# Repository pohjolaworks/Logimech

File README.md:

# Logimech
Replacement PCB for Logitech 3D Extreme joystick. Allows use of mechanical switches and MX keycaps for the side buttons of the joystick

## How to get
Gerber folder has plotted gerbers for the Rev 1 of Logimech. 
They were used to order from PCBWay, and should work atleast there.

## Notes:

Rev 1: User has reported some buttons physical location changed, this can be  fixed by remapping.

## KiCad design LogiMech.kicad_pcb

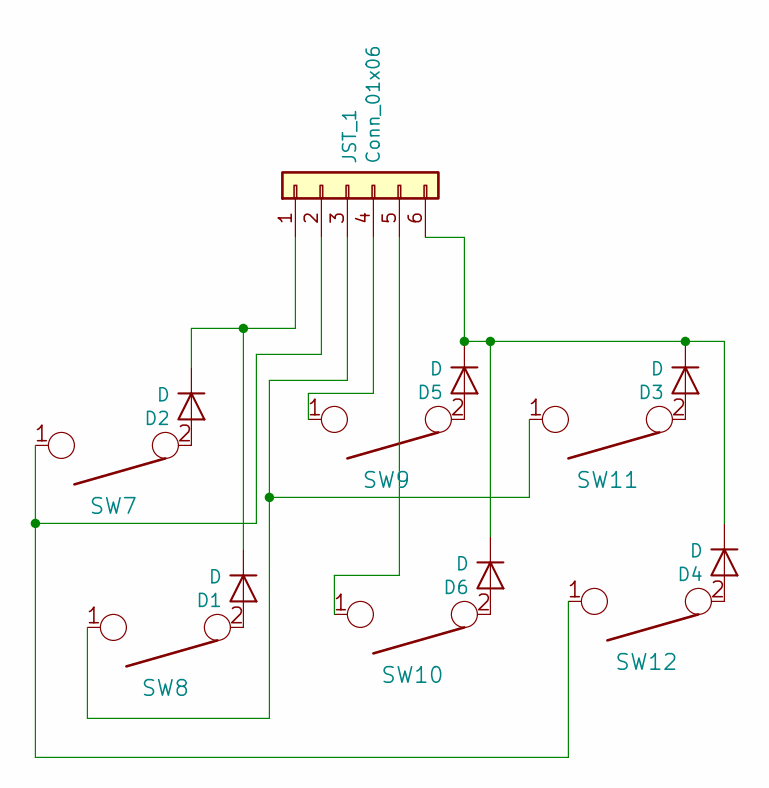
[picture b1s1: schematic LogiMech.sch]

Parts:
D1, D2, D3, D4, D5, D6: D; Diode-Hybrid-Back
JST_1: Conn_01x06; JST_XH_B6B-XH-A_1x06_P2.50mm_Vertical
SW7, SW8, SW9, SW10, SW11, SW12: KEYSW; kailh-cpg1353-reversible

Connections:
unnamed: D1.1 (K), D2.1 (K), JST_1.1
unnamed: D1.2 (A), SW8.2
unnamed: D2.2 (A), SW7.2
unnamed: D3.1 (K), D4.1 (K), D5.1 (K), D6.1 (K), JST_1.6
unnamed: D3.2 (A), SW11.2
unnamed: D4.2 (A), SW12.2
unnamed: D5.2 (A), SW9.2
unnamed: D6.2 (A), SW10.2
unnamed: JST_1.2, SW7.1, SW12.1
unnamed: JST_1.3, SW8.1, SW11.1
unnamed: JST_1.4, SW9.1
unnamed: JST_1.5, SW10.1

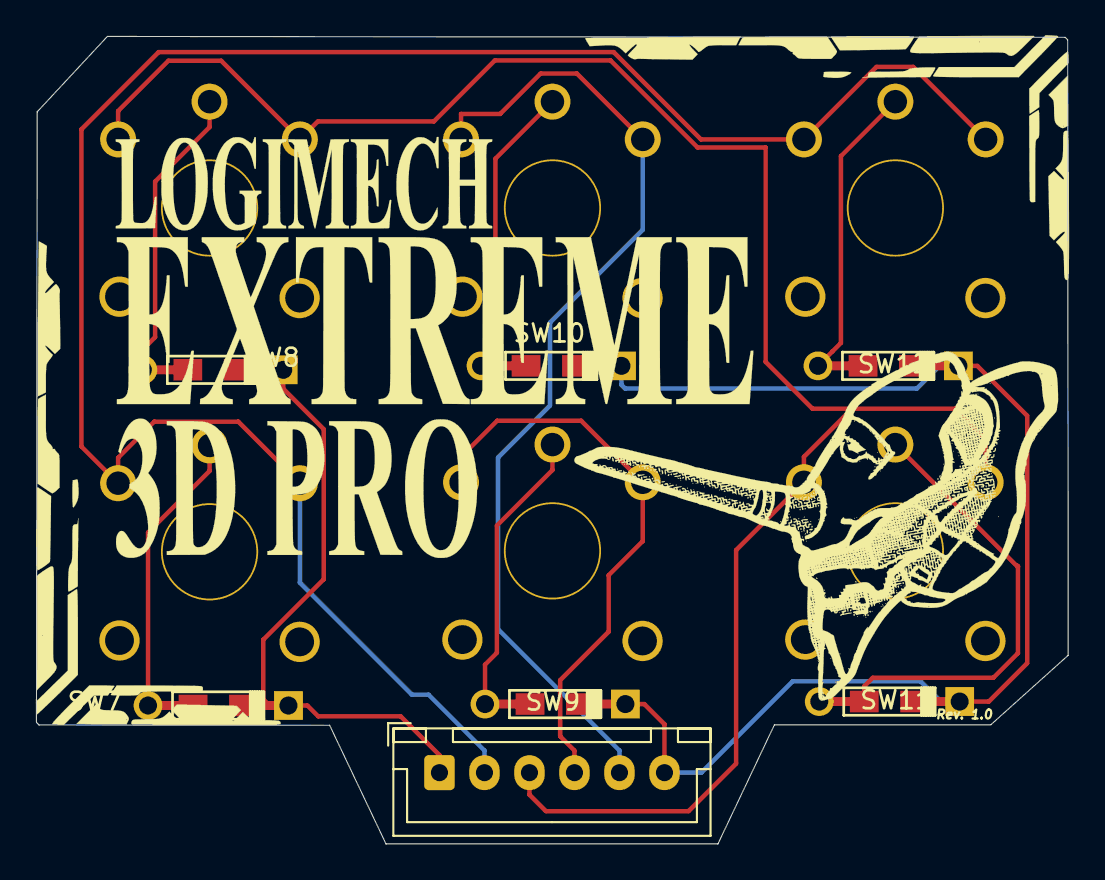
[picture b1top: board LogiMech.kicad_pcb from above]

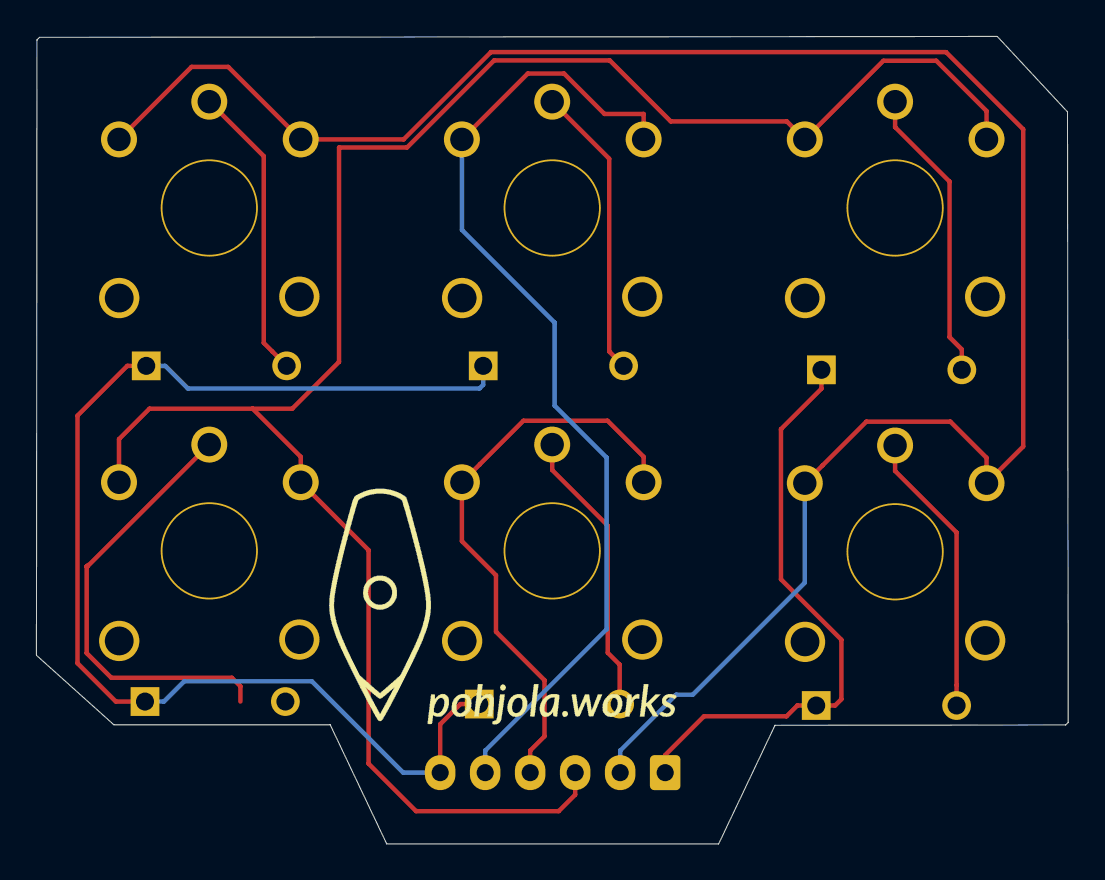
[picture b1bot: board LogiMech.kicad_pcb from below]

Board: 2 copper layers, 57.3 x 44.9 mm, 15 parts (6 on the bottom side), 12 nets.

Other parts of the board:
G_Logimech_text: LOGIMECH_TEXT; Logimech_text
LOGIMECHA: LOGIMECHA; LogiMech_Mecha

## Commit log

2020-11-17 Create LICENSE
2020-11-17 Initial commit, first version
